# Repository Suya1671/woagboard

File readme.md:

# Woagboard: Bisexual egg edition
_name chosen by popular vote._

**ROUND 3** This is the third hardware revision of the Woagboard keyboard. It's a 5x3 split ergonomic keyboard with 3 thumb keys on each half (36 keys total), inspired by the [TOTEM](https://github.com/GEIGEIGEIST/TOTEM).

I made this keyboard for myself, and to learn PCB design in the process. With the newest iteration, I've gotten into case design (Actually properly learning CAD for once), way more annoying part selection processes, and overall a chaotic time.

# Features

- 36 Keys
  - 5x3 matrix, with 3 thumb keys on each half
  - Splayed, column-staggered, ergonomic design
- Wireless, with generous space to fit a battery
  - 400mAh should last you a month
- On-board MCU
  - Nordic nRF52840, for BLE and USB-C connectivity
- Chaotic silkscreen printing
- Optional nice!view display mounting point
- RMK and ZMK firmware support

## The case

The case is designed to be 3D printed, with a focus on being thin, minimalistic, and clean. It features cutouts for all the necessary ports and buttons, and has a dedicated space for the nice!view display on the left half.
It also features cutouts for [Tenting Feet](https://www.aliexpress.com/item/1005005605228469.html) that make the keyboard way more comfy to use.

## The PCB

Silly, chaotic, yet somehow functional. The PCB is as small as the layout allows it to be, featuring an on-board Ebyte E73-2G4M08S1C module for wireless connectivity (Powered by the Nordic nRF52840), a BQ24075RGT battery charger (Which allows you to charge the keyboard while it's running. Such a revolutionary feature), and a 32.768kHz crystal for deep sleep functionality.

It also has really chaotic silkscreening. We stay silly.

### Schematic

:3

# BOM
This is the Bill of Materials (BOM) for 1 Woagboard (2 halves). This is why certain quanitites are doubled, as the board is two halves using the same PCB and components.
| Component                                      | Designator on PCB/Usage                            | Supplier     | Supplier URL                                            | Quantity                   |
| ---------------------------------------------- | -------------------------------------------------- | ------------ | ------------------------------------------------------- | -------------------------- |
| Woagboard PCB                                  | Placed in case                                     | JLCPCB       | See pcb/jlcpcb for production files                     | 2                          |
| Ebyte E73-2G4M08S1C MCU*                       | U1                                                 | LCSC         | <https://lcsc.com/product-detail/C356849.html>          | 2                          |
| TI BQ24075RGT Battery Charger                  | U2                                                 | LCSC         | <https://lcsc.com/product-detail/C15464.html>           | 2                          |
| Onsemi SRV05-4 ESD Protection                  | U3                                                 | LCSC         | <https://lcsc.com/product-detail/C2836319.html>         | 2                          |
| Korean Hroparts Elec TYPE-C-31-M-12            | J1                                                 | LCSC         | <https://lcsc.com/product-detail/C165948.html>          | 2                          |
| 1x6 Vertical Pin header                        | J2                                                 | LCSC         | <https://lcsc.com/product-detail/C706869.html>          | 2                          |
| Panasonic EVQ-P7C01P push button               | PWR1,RST1                                          | LCSC         | <https://lcsc.com/product-detail/C388883.html>          | 4                          |
| Yellow LED                                     | LED1                                               | LCSC         | <https://lcsc.com/product-detail/C2296.html>            | 2                          |
| Green LED                                      | LED2                                               | LCSC         | <https://lcsc.com/product-detail/C2297.html>            | 2                          |
| 4.7uF Capacitor                                | C2,C3,C4,C5                                        | LCSC         | <https://lcsc.com/product-detail/C23733.html>           | 8                          |
| 1uF Capacitor                                  | C1,C6                                              | LCSC         | <https://lcsc.com/product-detail/C52923.html>           | 4                          |
| 18pF Capacitor                                 | C7,C8                                              | LCSC         | <https://lcsc.com/product-detail/C1549.html>            | 4                          |
| 47kΩ Resistor                                  | R4                                                 | LCSC         | <https://lcsc.com/product-detail/C25792.html>           | 2                          |
| 10kΩ Resistor                                  | R7                                                 | LCSC         | <https://lcsc.com/product-detail/C25744.html>           | 2                          |
| 5.1kΩ Resistor                                 | R1,R2                                              | LCSC         | <https://lcsc.com/product-detail/C25905.html>           | 4                          |
| 3.9kΩ Resistor                                 | R6                                                 | LCSC         | <https://lcsc.com/product-detail/C23018.html>           | 2                          |
| 270Ω Resistor                                  | R3,R5,R8                                           | LCSC         | <https://lcsc.com/product-detail/C25867.html>           | 6                          |
| 750 mA fuse                                    | F1                                                 | LCSC         | <https://lcsc.com/product-detail/C2687878.html>         | 2                          |
| 32.768kHz Crystal                              | Y1                                                 | LCSC         | <https://lcsc.com/product-detail/C32346.html>           | 2                          |
| Murata Electronics BLM15PX121SN1D Ferrite Bead | L1                                                 | LCSC         | <https://lcsc.com/product-detail/C88970.html>           | 2                          |
| 10uH Inductor                                  | L2                                                 | LCSC         | <https://lcsc.com/product-detail/C223249.html>          | 2                          |
| Kailh PG1350 Choc Hotswap Sockets              | SW1-SW18                                           | AliExpress** | <https://www.aliexpress.com/item/1005004290562374.html> | 30 x 2 (36 used)           |
| Woagboard Case                                 | Surrounds PCB. Connected Via M2 screws             | 3D Printed   | See case for models                                     | 1x Left, 1x Right          |
| M2x10 Countersunk Screws                       | H1 (Mounting Point)                                | JKM          | <https://jkm.co.za/product/m2x10-csk-galv-m-screw-bos/> | 2                          |
| M2x12 Countersunk Screws                       | H2, H3 (Mounting Points)                           | JKM          | <https://jkm.co.za/product/m2x12-csk-galv-m-screw-bos/> | 4                          |
| M2 Brass Heat inserts                          | H1, H2, H3 (Mounting Points)                       | AliExpress   | <https://www.aliexpress.com/item/32890237459.html>      | 50 x 1 (6 M2 inserts used) |
| Laptop Tenting Feet                            | Attached to case                                   | AliExpress** | <https://www.aliexpress.com/item/1005005605228469.html> | 2 x 2                      |
| Choc switches                                  | SW1-SW18 (Connected via hotswap)                   | AliExpress   | <https://www.aliexpress.com/item/1005005883472162.html> | 30 x 2 (36 used)           |
| Choc keycaps                                   | SW1-SW18 (Connected via switch)                    | AliExpress   | <https://www.aliexpress.com/item/1005004558099208.html> | 50 x 1 (36 used)           |
| nice!view                                      | J4 (Wired up with wires. nice!view placed in case) | Typeractive  | <https://typeractive.xyz/products/nice-view>            | 1                          |

Notes:

- \* Alternativelty, the Ebyte E73-2G4M08S1CX can be used for a UFL connector, requiring an external antenna. Both options annoyingly got moved to standard assembly only while I was making this design, increasing costs dramatically (~$60 -> ~$100). I've contacted JLCPCB about this, and hopefully I can get it back on economic assembly for anybody else trying to make this board.
- ** Typeractive also has these. If you're in the US, might be better to buy from them instead.
- I already have switches and keycaps, so I don't need to purchase them.
- I am not purchasing the nice!view for the fact that I'm out of budget if I do. Thanks JLCPCB.

# Copyright notice
The Woagboard is not affiliated with New Blood Interactive, Tour De Pizza, or any other IPs referenced on the design.
I just like ULTRAKILL, Pizza Tower, etc.

- Keycap model taken from https://www.thingiverse.com/thing:4564253 (CC BY-NC)
- Keyswitch model taken from https://github.com/kiswitch/kiswitch
- nice!view model taken from https://www.printables.com/model/1114611-niceview-oled/files (CC BY-NC)
- Neocats from https://volpeon.ink/emojis/neocat/ (CC-BY-NC-SA-4.0)
- Neofox from https://volpeon.ink/emojis/neofox/ (CC-BY-NC-SA-4.0)
- Neodog from https://git.gay/moonrabbits/neodog/src/branch/main/neodog/neodog.png (CC-BY-NC-SA-4.0)
- Neorat from https://emoji-repo.absturztau.be/repo/neorat.zip (CC-BY-NC-SA-4.0)
- Neobread from https://github.com/olivvybee/emojis/blob/main/neobread/neobread.svg (CC-BY-NC-SA-4.0)
- Neobot from https://github.com/SymTrkl/emoji/blob/main/webres/neobot/neobot.png (CC-BY-NC-SA-4.0)
- Monadic Cat's mask from https://www.catmonad.xyz/pfp.html (CC-BY-SA-4.0)

The board's actual license is the CERN Open Hardware License v1.2. See the [license file](./license.md) for more information.

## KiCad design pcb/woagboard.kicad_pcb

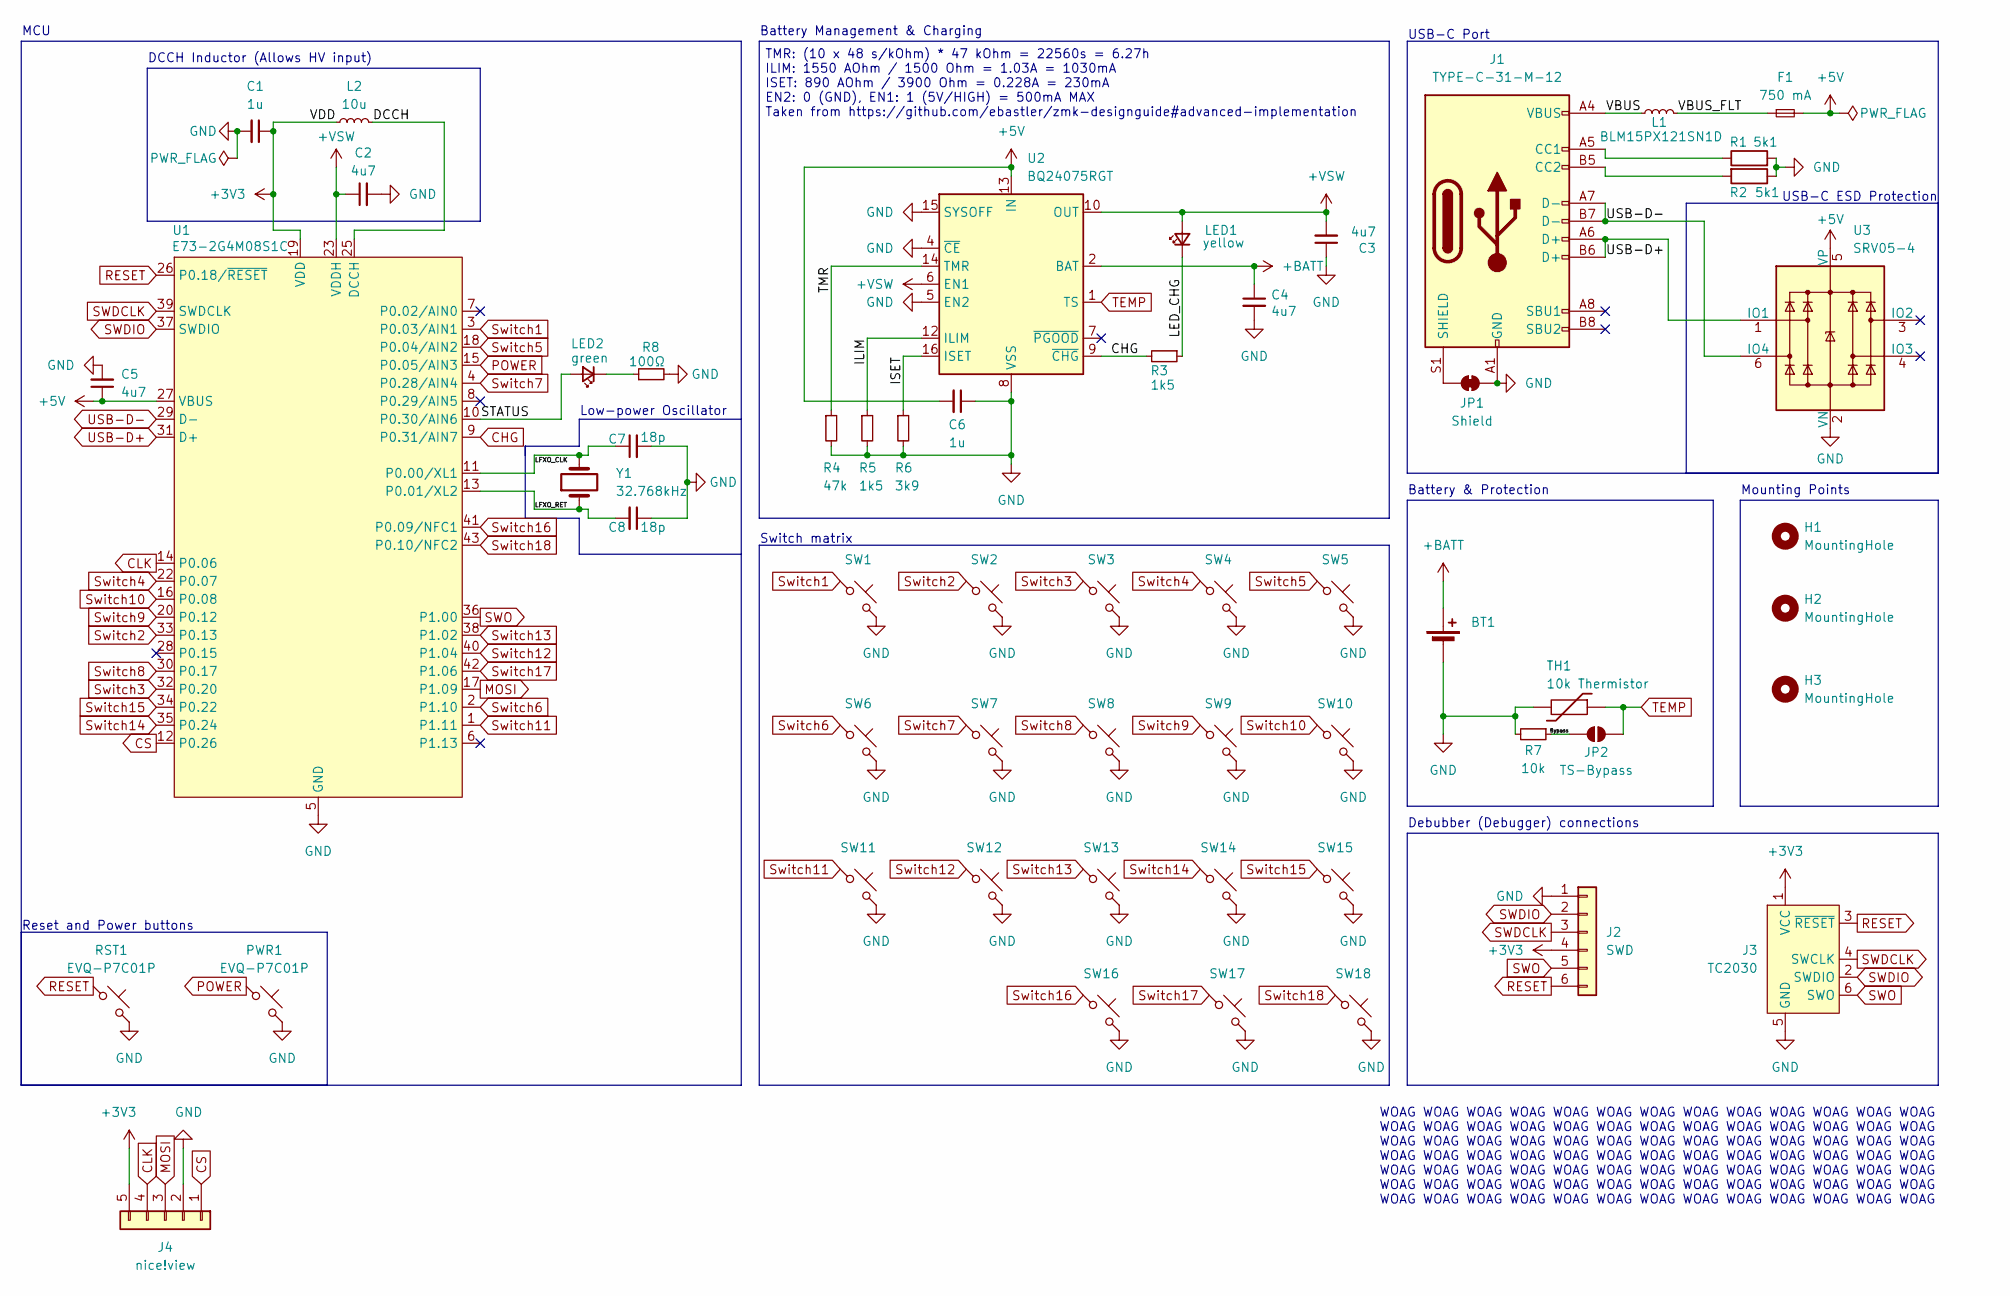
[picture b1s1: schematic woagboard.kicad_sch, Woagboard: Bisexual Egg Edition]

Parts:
BT1: Battery_Cell; JST_PH_S2B-PH-K_1x02_P2.00mm_Horizontal
C1, C6: 1u; C_0402_1005Metric_Pad0.74x0.62mm_HandSolder; LCSC C52923
C2, C3, C4, C5: 4u7; C_0402_1005Metric_Pad0.74x0.62mm_HandSolder; LCSC C23733
C7, C8: 18p; C_0402_1005Metric_Pad0.74x0.62mm_HandSolder; LCSC C1549
F1: 750 mA; Fuse_0603_1608Metric; LCSC C2687878
H1, H2, H3: MountingHole; MountingHole_2.2mm_M2
J1: TYPE-C-31-M-12; USB_C_Receptacle_HRO_TYPE-C-31-M-12; LCSC C165948
J2: SWD; PinHeader_1x06_P2.54mm_Horizontal; LCSC C706869
J3: TC2030; Tag-Connect_TC2030-IDC-FP_2x03_P1.27mm_Vertical
J4: nice!view; nice!view_pads
JP1: Shield; SolderJumper-2_P1.3mm_Bridged_RoundedPad1.0x1.5mm
JP2: TS-Bypass; SolderJumper-2_P1.3mm_Open_RoundedPad1.0x1.5mm
L1: BLM15PX121SN1D; L_0402_1005Metric; LCSC C88970
L2: 10u; L_0805_2012Metric_Pad1.15x1.40mm_HandSolder; LCSC C223249
LED1: yellow; LED_0805_2012Metric_Pad1.15x1.40mm_HandSolder; LCSC C2296
LED2: green; LED_0805_2012Metric_Pad1.15x1.40mm_HandSolder; LCSC C2297
PWR1: EVQ-P7C01P; LCSC C388883
R1, R2: 5k1; R_0402_1005Metric_Pad0.72x0.64mm_HandSolder; LCSC C25905
R3: 1k5; R_0603_1608Metric_Pad0.98x0.95mm_HandSolder; LCSC C25867
R4: 47k; R_0402_1005Metric_Pad0.72x0.64mm_HandSolder; LCSC C25792
R5: 1k5; R_0402_1005Metric_Pad0.72x0.64mm_HandSolder; LCSC C25867
R6: 3k9; R_0603_1608Metric_Pad0.98x0.95mm_HandSolder; LCSC C23018
R7: 10k; R_0402_1005Metric_Pad0.72x0.64mm_HandSolder; LCSC C25744
R8: 100Ω; R_0603_1608Metric_Pad0.98x0.95mm_HandSolder; LCSC C25867
RST1: EVQ-P7C01P; LCSC C388883
SW1, SW2, SW3, SW4, SW5, SW6, SW7, SW8, SW9, SW10, SW11, SW12, SW13, SW14, SW15, SW16, SW17, SW18: SW_Push_45deg; Choc-V1-HS-Reversible
TH1: 10k Thermistor; TestPoint_2Pads_Pitch2.54mm_Drill0.8mm
U1: E73-2G4M08S1C; nRF52840_E73-2G4M08S1C; LCSC C356849
U2: BQ24075RGT; QFN-16-1EP_3x3mm_P0.5mm_EP1.7x1.7mm; LCSC C15464
U3: SRV05-4; SOT-23-6-routable; LCSC C2836319
Y1: 32.768kHz; Q13FC13500004; LCSC C32346

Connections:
+3V3: C1.1, J2.4, J3.1 (VCC), J4.5, L2.1, U1.19 (VDD)
+5V: C5.1, C6.2, F1.2, U1.27 (VBUS), U2.13 (IN), U3.5 (VP)
+BATT: BT1.1 (+), C4.1, U2.2 (BAT), U2.3 (BAT)
+VSW: C2.1, C3.2, LED1.2 (A), U1.23 (VDDH), U2.6 (EN1), U2.10 (OUT), U2.11 (OUT)
/Bypass: JP2.1 (A), R7.1
/DCCH: L2.2, U1.25 (DCCH)
/ILIM: R5.1, U2.12 (ILIM)
/ISET: R6.1, U2.16 (ISET)
/LED_CHG: LED1.1 (K), R3.1
/LFXO_CLK: C7.1, U1.11 (P0.00/XL1), Y1.2
/LFXO_RET: C8.2, U1.13 (P0.01/XL2), Y1.1
/STATUS: LED2.2 (A), U1.10 (P0.30/AIN6)
/TMR: R4.1, U2.14 (TMR)
/VBUS: J1.A4 (VBUS), J1.A9 (VBUS), J1.B4 (VBUS), J1.B9 (VBUS), L1.1
/VBUS_FLT: F1.1, L1.2
CHG: R3.2, U1.9 (P0.31/AIN7), U2.9 (~CHG)
CLK: J4.4, U1.14 (P0.06)
CS: J4.1, U1.12 (P0.26)
GND: BT1.2 (-), C1.2, C2.2, C3.1, C4.2, C5.2, C6.1, C7.2, C8.1, J1.A1 (GND), J1.A12 (GND), J1.B1 (GND), J1.B12 (GND), J2.1, J3.5 (GND), J4.2, JP1.1 (A), PWR1.2, R1.2, R2.1, R4.2, R5.2, R6.2, R7.2, R8.2, RST1.2, SW1.2, SW2.2, SW3.2, SW4.2, SW5.2, SW6.2, SW7.2, SW8.2, SW9.2, SW10.2, SW11.2, SW12.2, SW13.2, SW14.2, SW15.2, SW16.2, SW17.2, SW18.2, TH1.2, U1.5 (GND), U1.21 (GND), U1.24 (GND), U2.4 (~CE), U2.5 (EN2), U2.8 (VSS), U2.15 (SYSOFF), U2.17 (VSS), U3.2 (VN)
MOSI: J4.3, U1.17 (P1.09)
unnamed: J1.A5 (CC1), R1.1
unnamed: J1.B5 (CC2), R2.2
unnamed: J1.S1 (SHIELD), JP1.2 (B)
unnamed: LED2.1 (K), R8.1
POWER: PWR1.1, U1.15 (P0.05/AIN3)
RESET: J2.6, J3.3 (~RESET), RST1.1, U1.26 (P0.18/~RESET)
SWDCLK: J2.3, J3.4 (SWCLK), U1.39 (SWDCLK)
SWDIO: J2.2, J3.2 (SWDIO), U1.37 (SWDIO)
SWO: J2.5, J3.6 (SWO), U1.36 (P1.00)
Switch1: SW1.1, U1.3 (P0.03/AIN1)
Switch2: SW2.1, U1.33 (P0.13)
Switch3: SW3.1, U1.32 (P0.20)
Switch4: SW4.1, U1.22 (P0.07)
Switch5: SW5.1, U1.18 (P0.04/AIN2)
Switch6: SW6.1, U1.2 (P1.10)
Switch7: SW7.1, U1.4 (P0.28/AIN4)
Switch8: SW8.1, U1.30 (P0.17)
Switch9: SW9.1, U1.20 (P0.12)
Switch10: SW10.1, U1.16 (P0.08)
Switch11: SW11.1, U1.1 (P1.11)
Switch12: SW12.1, U1.40 (P1.04)
Switch13: SW13.1, U1.38 (P1.02)
Switch14: SW14.1, U1.35 (P0.24)
Switch15: SW15.1, U1.34 (P0.22)
Switch16: SW16.1, U1.41 (P0.09/NFC1)
Switch17: SW17.1, U1.42 (P1.06)
Switch18: SW18.1, U1.43 (P0.10/NFC2)
TEMP: JP2.2 (B), TH1.1, U2.1 (TS)
USB-D+: J1.A6 (D+), J1.B6 (D+), U1.31 (D+), U3.1 (IO1)
USB-D-: J1.A7 (D-), J1.B7 (D-), U1.29 (D-), U3.6 (IO4)

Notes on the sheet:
WOAG WOAG WOAG WOAG WOAG WOAG WOAG WOAG WOAG WOAG WOAG WOAG WOAG WOAG WOAG WOAG WOAG WOAG WOAG WOAG WOAG WOAG WOAG WOAG WOAG WOAG WOAG WOAG WOAG WOAG WOAG WOAG WOAG WOAG WOAG WOAG WOAG WOAG WOAG WOAG WOAG WOAG WOAG WOAG WOAG WOAG WOAG WOAG WOAG WOAG WOAG WOAG WOAG WOAG WOAG WOAG WOAG WOAG WOAG WOAG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
DCCH Inductor (Allows HV input)
Mounting Points
Debubber (Debugger) connections
Battery & Protection
USB-C ESD Protection
Switch matrix
USB-C Port
Low-power Oscillator
MCU
TMR: (10 x 48 s/kOhm) * 47 kOhm = 22560s = 6.27h ILIM: 1550 AOhm / 1500 Ohm = 1.03A = 1030mA ISET: 890 AOhm / 3900 Ohm = 0.228A = 230mA EN2: 0 (GND), EN1: 1 (5V/HIGH) = 500mA MAX Taken from https://github.com/ebastler/zmk-designguide#advanced-implementation
Battery Management & Charging
Reset and Power buttons

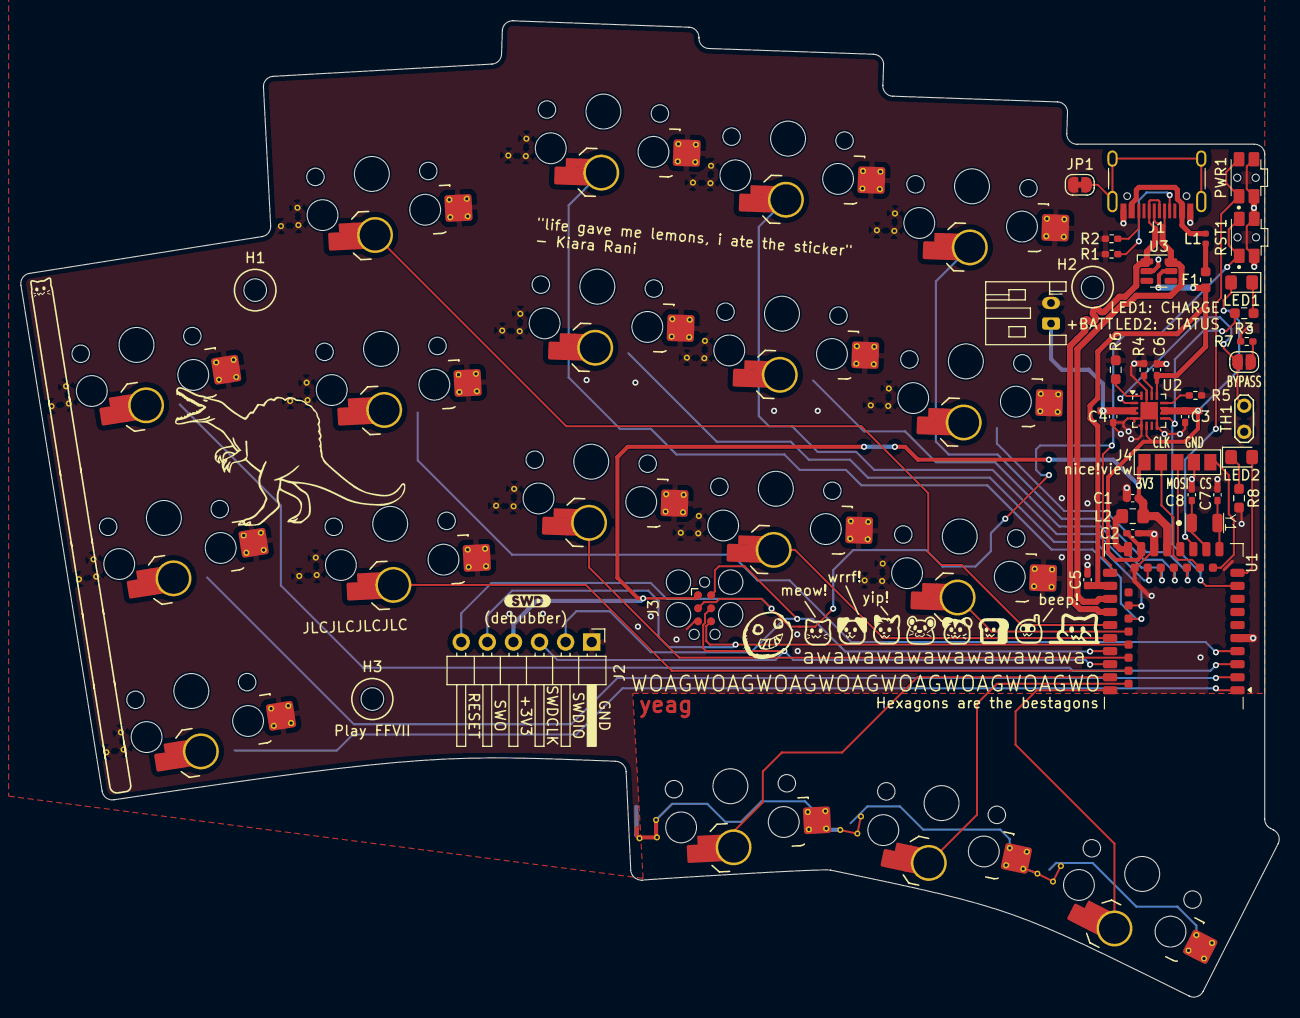
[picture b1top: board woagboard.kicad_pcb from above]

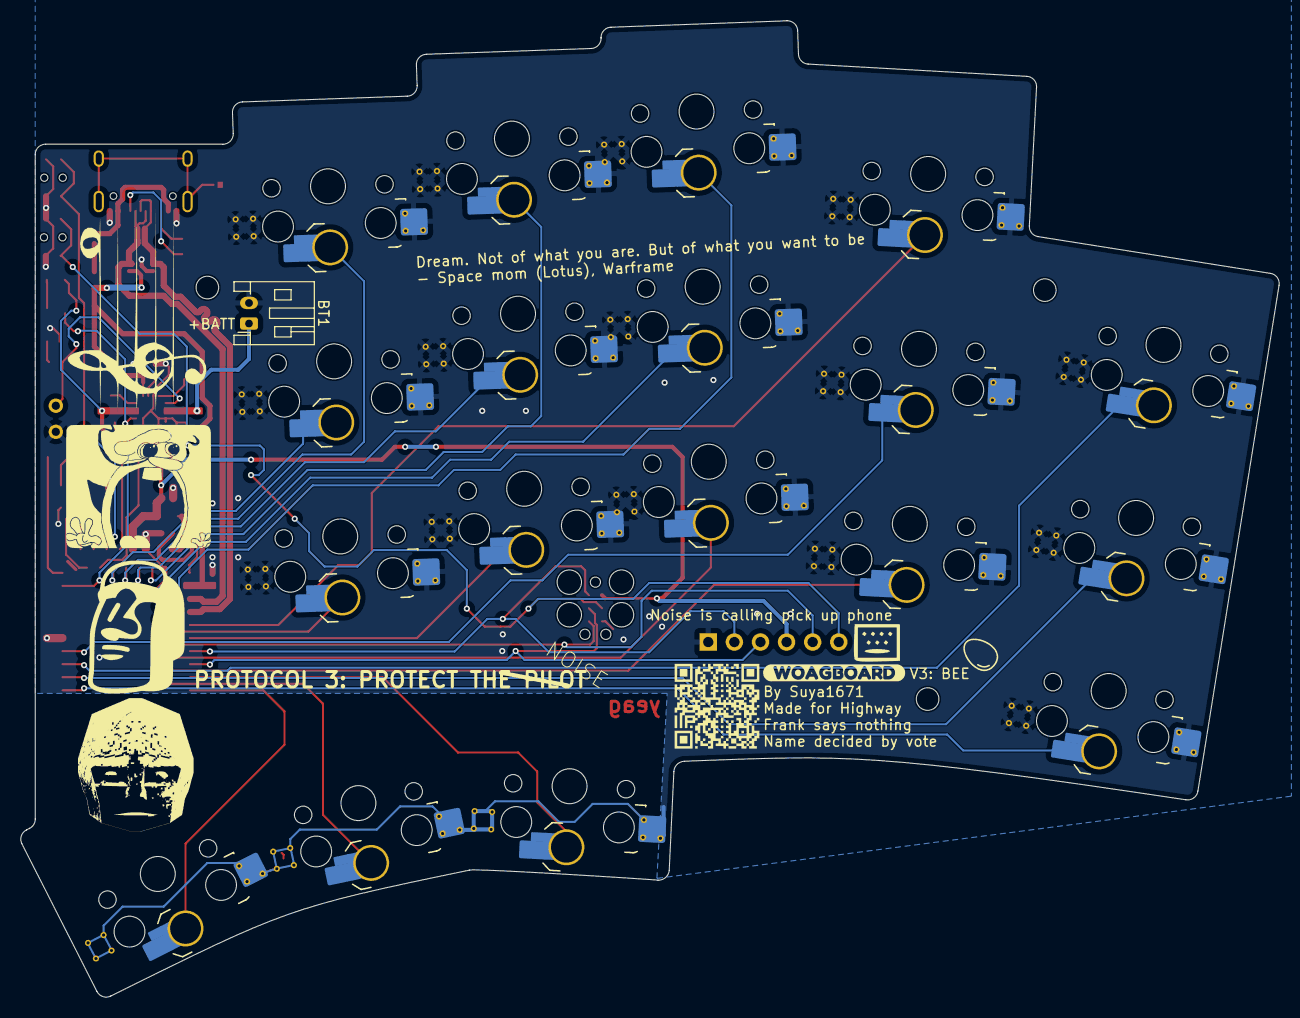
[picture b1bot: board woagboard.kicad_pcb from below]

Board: 2 copper layers, 122.5 x 95.0 mm, 59 parts (3 on the bottom side), 50 nets.

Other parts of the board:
QR*****: WobblQR
kibuzzard-686125E5: G***; kibuzzard-686125E5
kibuzzard-686573C8: G***; kibuzzard-686573C8

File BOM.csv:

"Component"                                     , "Designator on PCB/Usage"                           , "Supplier"   , "Supplier URL"                                                               , "Quantity"
"Woagboard PCB"                                 , "Placed in case"                                    , "JLCPCB"     , "See pcb/jlcpcb for production files"                                        , "2"
"Ebyte E73-2G4M08S1C MCU*"                      , "U1"                                                , "LCSC"       , "<https://lcsc.com/product-detail/C356849.html>"                             , "2"
"TI BQ24075RGT Battery Charger"                 , "U2"                                                , "LCSC"       , "<https://lcsc.com/product-detail/C15464.html>"                              , "2"
"Onsemi SRV05-4 ESD Protection"                 , "U3"                                                , "LCSC"       , "<https://lcsc.com/product-detail/C2836319.html>"                            , "2"
"Korean Hroparts Elec TYPE-C-31-M-12"           , "J1"                                                , "LCSC"       , "<https://lcsc.com/product-detail/C165948.html>"                             , "2"
"1x6 Vertical Pin header"                       , "J2"                                                , "LCSC"       , "<https://lcsc.com/product-detail/C706869.html>"                             , "2"
"Panasonic EVQ-P7C01P push button"              , "PWR1,RST1"                                         , "LCSC"       , "<https://lcsc.com/product-detail/C388883.html>"                             , "4"
"Yellow LED"                                    , "LED1"                                              , "LCSC"       , "<https://lcsc.com/product-detail/C2296.html>"                               , "2"
"Green LED"                                     , "LED2"                                              , "LCSC"       , "<https://lcsc.com/product-detail/C2297.html>"                               , "2"
"4.7uF Capacitor"                               , "C2,C3,C4,C5"                                       , "LCSC"       , "<https://lcsc.com/product-detail/C23733.html>"                              , "8"
"1uF Capacitor"                                 , "C1,C6"                                             , "LCSC"       , "<https://lcsc.com/product-detail/C52923.html>"                              , "4"
"18pF Capacitor"                                , "C7,C8"                                             , "LCSC"       , "<https://lcsc.com/product-detail/C1549.html>"                               , "4"
"47kΩ Resistor"                                 , "R4"                                                , "LCSC"       , "<https://lcsc.com/product-detail/C25792.html>"                              , "2"
"10kΩ Resistor"                                 , "R7"                                                , "LCSC"       , "<https://lcsc.com/product-detail/C25744.html>"                              , "2"
"5.1kΩ Resistor"                                , "R1,R2"                                             , "LCSC"       , "<https://lcsc.com/product-detail/C25905.html>"                              , "4"
"3.9kΩ Resistor"                                , "R6"                                                , "LCSC"       , "<https://lcsc.com/product-detail/C23018.html>"                              , "2"
"270Ω Resistor"                                 , "R3,R5,R8"                                          , "LCSC"       , "<https://lcsc.com/product-detail/C25867.html>"                              , "6"
"750 mA fuse"                                   , "F1"                                                , "LCSC"       , "<https://lcsc.com/product-detail/C2687878.html>"                            , "2"
"32.768kHz Crystal"                             , "Y1"                                                , "LCSC"       , "<https://lcsc.com/product-detail/C32346.html>"                              , "2"
"Murata Electronics BLM15PX121SN1D Ferrite Bead", "L1"                                                , "LCSC"       , "<https://lcsc.com/product-detail/C88970.html>"                              , "2"
"10uH Inductor"                                 , "L2"                                                , "LCSC"       , "<https://lcsc.com/product-detail/C223249.html>"                             , "2"
"Kailh PG1350 Choc Hotswap Sockets"             , "SW1-SW18"                                          , "Typeractive", "<https://typeractive.xyz/products/hotswap-sockets?variant=457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", "10 x 4 (36 used)"
"Woagboard Case"                                , "Surrounds PCB. Connected Via M2 screws"            , "3D Printed" , "See case for models"                                                        , "1x Left, 1x Right"
"M2x10 Countersunk Screws"                      , "H1 (Mounting Point)"                               , "JKM"        , "<https://jkm.co.za/product/m2x10-csk-galv-m-screw-bos/>"                    , "2"
"M2x12 Countersunk Screws"                      , "H2, H3 (Mounting Points)"                          , "JKM"        , "<https://jkm.co.za/product/m2x12-csk-galv-m-screw-bos/>"                    , "4"
"M2 Brass Heat inserts"                         , "H1, H2, H3 (Mounting Points)"                      , "AliExpress" , "<https://www.aliexpress.com/item/32890237459.html>"                         , "50 x 1 (6 M2 inserts used)"
"Laptop Tenting Feet"                           , "Attached to case"                                  , "Typeractive", "<https://typeractive.xyz/products/tenting-feet>**"                          , "2 x 2"
"Choc switches"                                 , "SW1-SW18 (Connected via hotswap)"                  , "AliExpress" , "<https://www.aliexpress.com/item/1005005883472162.html>***"                 , "30 x 2 (36 used)"
"Choc keycaps"                                  , "SW1-SW18 (Connected via switch)"                   , "AliExpress" , "<https://www.aliexpress.com/item/1005004558099208.html>***"                 , "50 x 1 (36 used)"
"nice!view"                                     , "J4 (Wired up with wires. nice!view placed in case)", "Typeractive", "<https://typeractive.xyz/products/nice-view>"                               , "1"

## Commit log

2024-09-07 feat: inital yaml file for the woagboard and removed unneeded kicad schematics
2024-09-07 fix: fix a stupid
2024-09-08 design: adjust inner column stagger
2024-09-08 pcb: start working on pcb design
2024-09-11 wip: finish left half and start work on right half
2024-09-13 wip: initial pcb of full woagboard
    note: Do not print this. It's not even close to ready probably
2024-09-14 fix: much better routing
2024-09-15 pcb: more pcb design and silkscreen shenanigains
2024-09-16 chore: move some traces
2024-09-16 feat: better usb trace impedance and silkscreen shenangains
2024-09-17 chore: more silkscreen stuffs
2024-09-17 feat: RC1
2024-09-17 chore: generate manufacturing files
2024-09-17 pcb: replace oscillator
2024-09-23 wip(pcb): heavy wip on woagboard v0.2
    - new usb port
    - redoing routing again
    - soldering + hotswap in one
2024-09-26 feat: woagboard V0.2 REV1
2024-09-26 feat: better DCCH loop
2024-09-27 feat: better grounding and positioning
2024-09-27 chore: remove vcut comment
2024-10-05 feat: add bootloader
2024-10-16 fix: fix the single biggest mistake on the board
    I blew up the left half because of this missing trace. No idea how to fix my current boards now....
2025-06-28 feat: yeet existing design and replace with modified yeagboard
2025-06-28 feat: add new pcb files
2025-06-29 feat: initial pcb
2025-07-02 feat: reorganise and add basic case files
2025-07-03 feat: add larger files
2025-07-13 feat: add case
2025-07-14 feat: add rust firmware
2025-07-14 chore: yeet nix file
2025-07-15 feat: updated production files
2025-07-15 feat: add silkscreen image
2025-07-15 chore; remove unnessesary * in BOM
2025-07-16 feat: add renders
2025-07-16 feat: add zmk firmware
2025-07-16 feat: add in case stl files
2025-07-16 docs: fix typo
2025-07-25 chore: move production files to dedicated folter
